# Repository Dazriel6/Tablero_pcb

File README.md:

Tablero de basquetball utilizando dos PCB (potencia y control) para poder comunicarme mediante wifi al tablero y realizar los cambios necesarios.

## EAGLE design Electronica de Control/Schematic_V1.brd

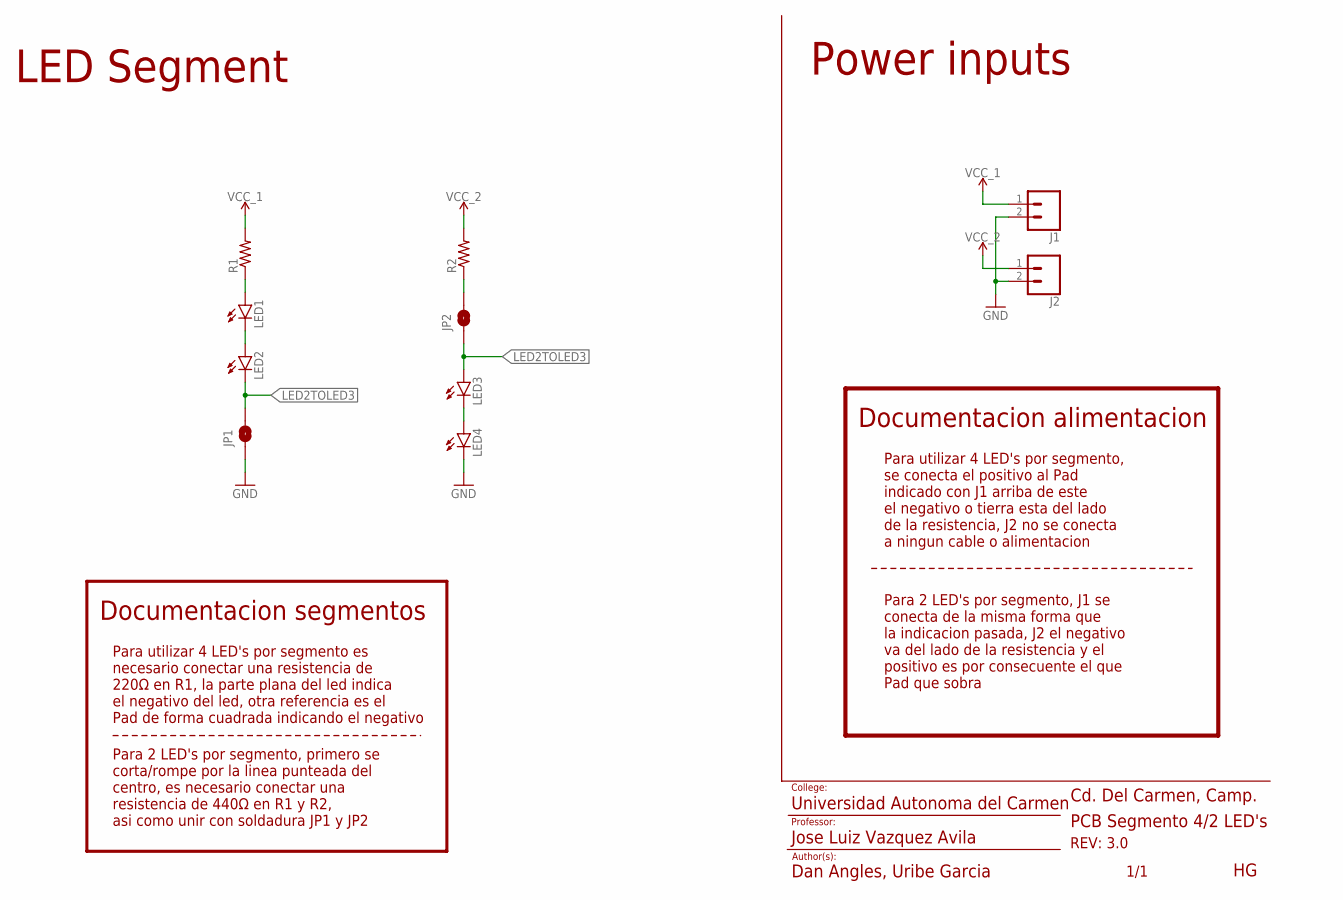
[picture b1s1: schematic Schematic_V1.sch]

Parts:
J1, J2: CONN_02LOCK; 1X02_LOCK
JP1, JP2: JUMPER-SMT_2_NO_SILK_ROUND; SMT-JUMPER_2_NO_SILK_ROUND
LED1, LED2, LED3, LED4: LED10MM
R1, R2: R-US_0411/3V; 0411V

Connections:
GND: J1.2, J2.2, JP1.1, LED4.K (C)
LED2TOLED3: JP1.2, JP2.1, LED2.K (C), LED3.A
unnamed: LED1.K (C), LED2.A
unnamed: LED1.A, R1.1
unnamed: LED3.K (C), LED4.A
unnamed: JP2.2, R2.1
VCC_1: J1.1, R1.2
VCC_2: J2.1, R2.2

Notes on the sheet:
REV: 3.0
Universidad Autonoma del Carmen
Cd. Del Carmen, Camp.
Jose Luiz Vazquez Avila
Dan Angles, Uribe Garcia
College:
Professor:
Author(s):
1/1
LED Segment
Power inputs
Documentacion segmentos
Para utilizar 4 LED's por segmento es necesario conectar una resistencia de 220Ω en R1, la parte plana del led indica el negativo del led, otra referencia es el Pad de forma cuadrada indicando el negativo
Para 2 LED's por segmento, primero se corta/rompe por la linea punteada del centro, es necesario conectar una resistencia de 440Ω en R1 y R2, asi como unir con soldadura JP1 y JP2
Documentacion alimentacion
Para utilizar 4 LED's por segmento, se conecta el positivo al Pad indicado con J1 arriba de este el negativo o tierra esta del lado de la resistencia, J2 no se conecta a ningun cable o alimentacion
Para 2 LED's por segmento, J1 se conecta de la misma forma que la indicacion pasada, J2 el negativo va del lado de la resistencia y el positivo es por consecuente el que Pad que sobra
PCB Segmento 4/2 LED's

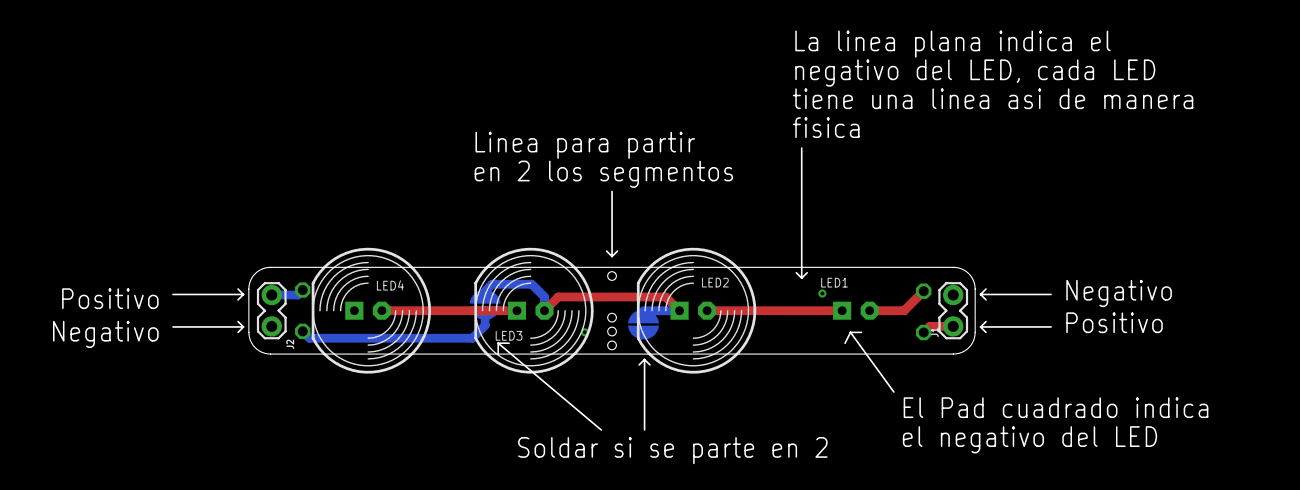
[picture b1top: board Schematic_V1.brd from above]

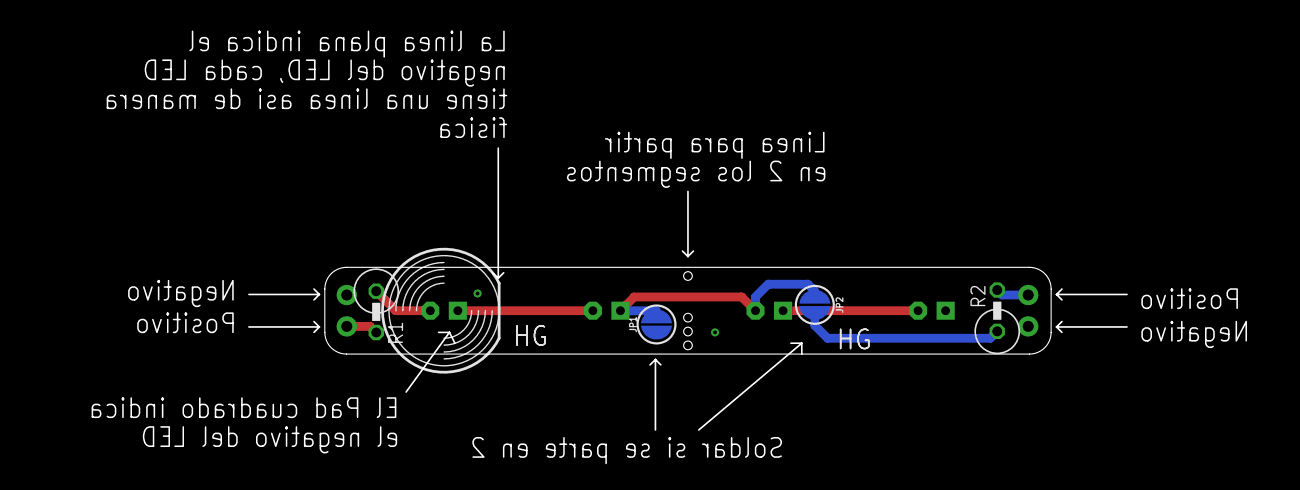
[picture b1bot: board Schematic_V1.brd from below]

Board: 2 copper layers, 115.8 x 41.1 mm, 10 parts (5 on the bottom side), 8 nets.

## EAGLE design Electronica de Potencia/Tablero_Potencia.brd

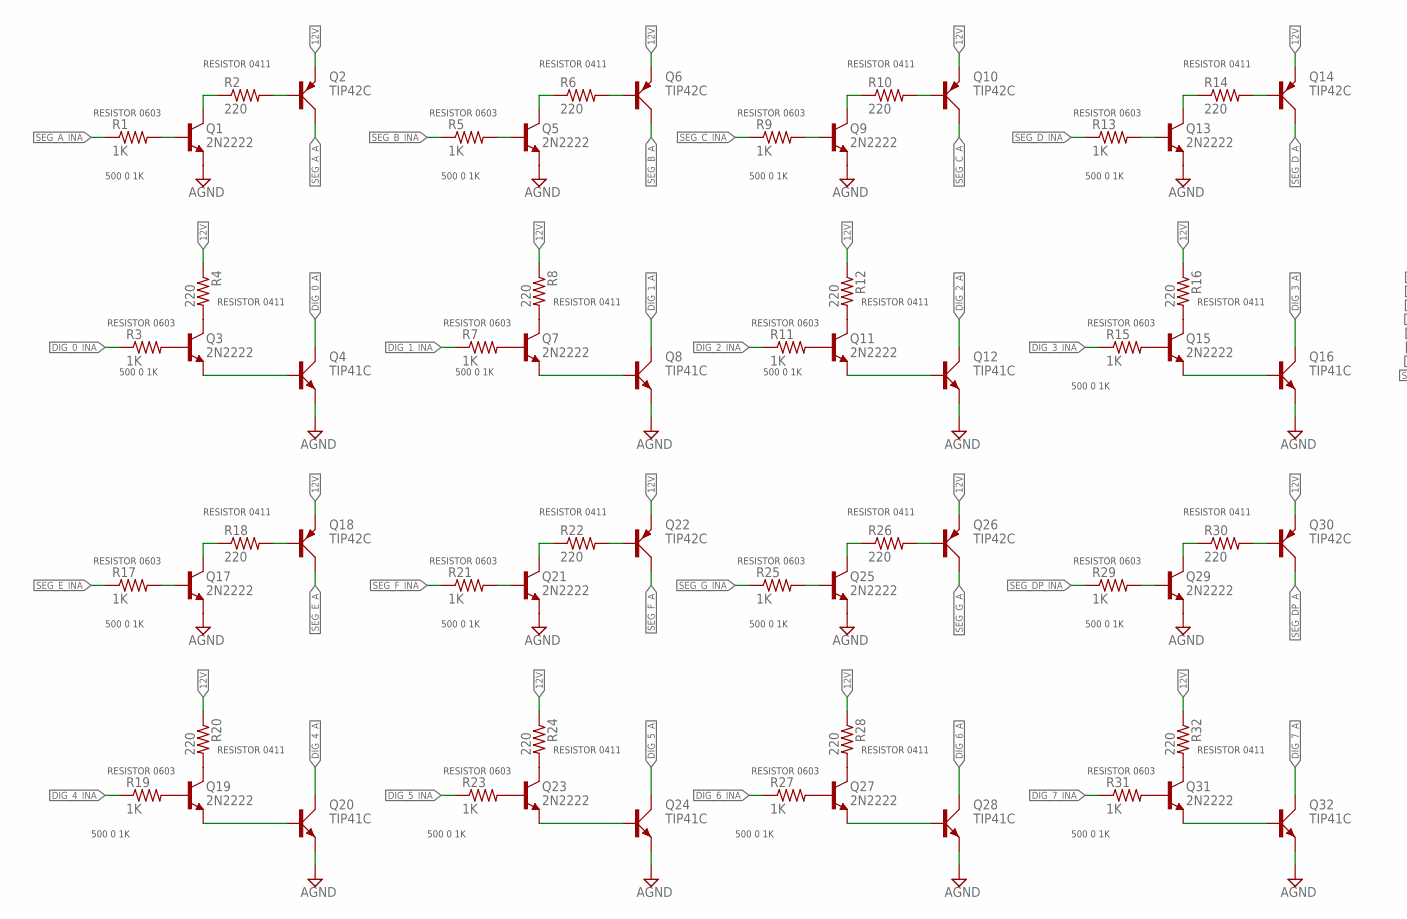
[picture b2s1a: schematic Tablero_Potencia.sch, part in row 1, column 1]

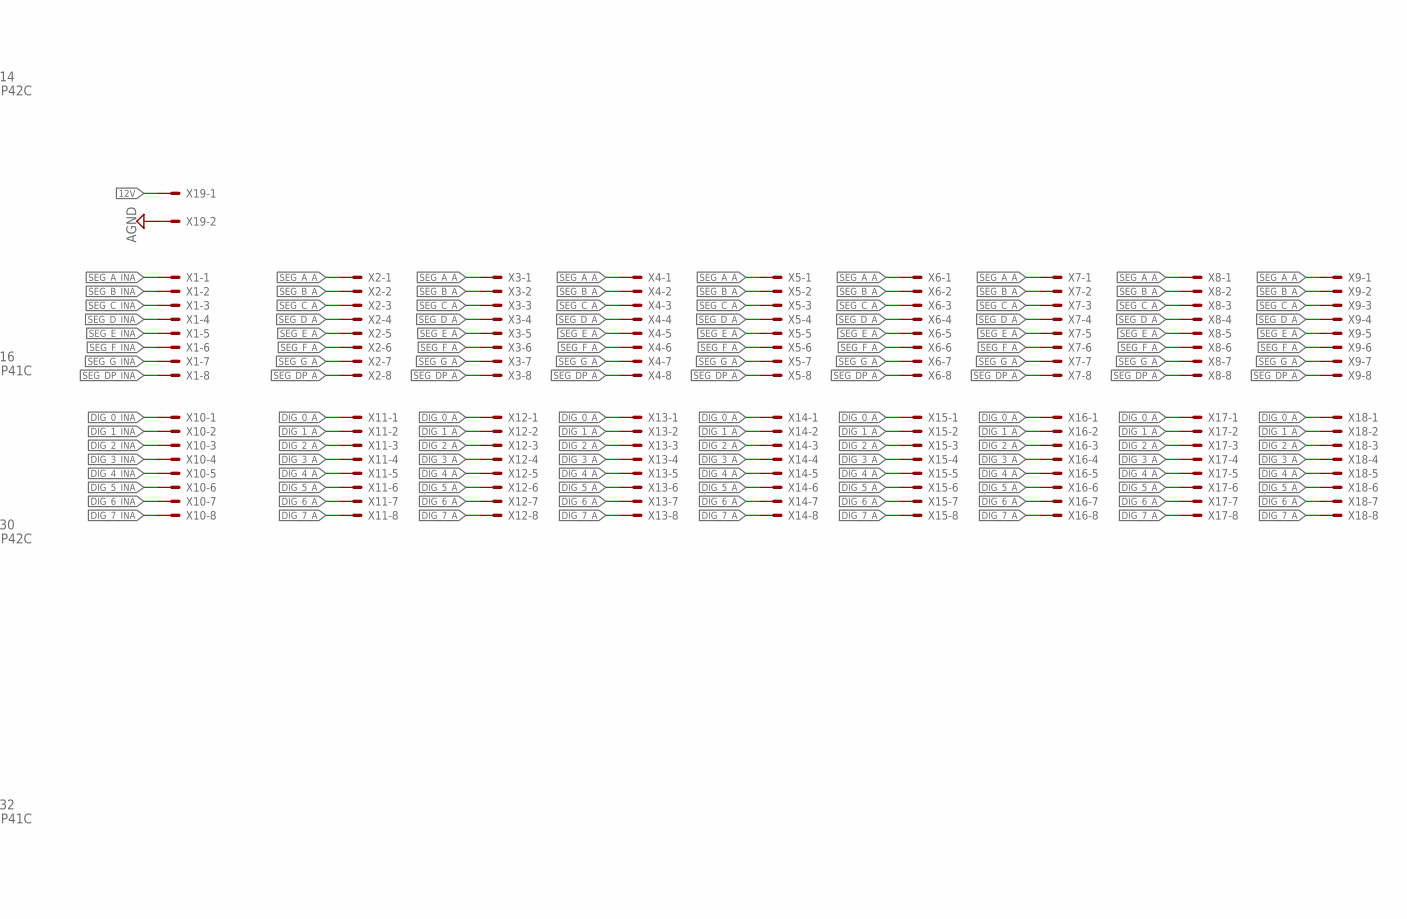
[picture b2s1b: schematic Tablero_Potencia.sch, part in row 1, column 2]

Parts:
Q1, Q3, Q5, Q7, Q9, Q11, Q13, Q15, Q17, Q19, Q21, Q23, Q25, Q27, Q29, Q31: 2N2222; TO92
Q2, Q6, Q10, Q14, Q18, Q22, Q26, Q30: TIP42C; TO220AV
Q4, Q8, Q12, Q16, Q20, Q24, Q28, Q32: TIP41C; TO220AV
R1, R3, R5, R7, R9, R11, R13, R15, R17, R19, R21, R23, R25, R27, R29, R31: 1K; R0603
R2, R4, R6, R8, R10, R12, R14, R16, R18, R20, R22, R24, R26, R28, R30, R32: 220; 0411/15
X1, X2, X3, X4, X5, X6, X7, X8, X9, X10, X11, X12, X13, X14, X15, X16, X17, X18: KK-156-8
X19: KK-156-2

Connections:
12V: Q2.E, Q6.E, Q10.E, Q14.E, Q18.E, Q22.E, Q26.E, Q30.E, R4.1, R8.1, R12.1, R16.1, R20.1, R24.1, R28.1, R32.1, X19.1
AGND: Q1.3 (E), Q4.E, Q5.3 (E), Q8.E, Q9.3 (E), Q12.E, Q13.3 (E), Q16.E, Q17.3 (E), Q20.E, Q21.3 (E), Q24.E, Q25.3 (E), Q28.E, Q29.3 (E), Q32.E, X19.2
DIG_0_A: Q4.C, X11.1, X12.1, X13.1, X14.1, X15.1, X16.1, X17.1, X18.1
DIG_0_INA: R3.1, X10.1
DIG_1_A: Q8.C, X11.2, X12.2, X13.2, X14.2, X15.2, X16.2, X17.2, X18.2
DIG_1_INA: R7.1, X10.2
DIG_2_A: Q12.C, X11.3, X12.3, X13.3, X14.3, X15.3, X16.3, X17.3, X18.3
DIG_2_INA: R11.1, X10.3
DIG_3_A: Q16.C, X11.4, X12.4, X13.4, X14.4, X15.4, X16.4, X17.4, X18.4
DIG_3_INA: R15.1, X10.4
DIG_4_A: Q20.C, X11.5, X12.5, X13.5, X14.5, X15.5, X16.5, X17.5, X18.5
DIG_4_INA: R19.1, X10.5
DIG_5_A: Q24.C, X11.6, X12.6, X13.6, X14.6, X15.6, X16.6, X17.6, X18.6
DIG_5_INA: R23.1, X10.6
DIG_6_A: Q28.C, X11.7, X12.7, X13.7, X14.7, X15.7, X16.7, X17.7, X18.7
DIG_6_INA: R27.1, X10.7
DIG_7_A: Q32.C, X11.8, X12.8, X13.8, X14.8, X15.8, X16.8, X17.8, X18.8
DIG_7_INA: R31.1, X10.8
unnamed: Q2.B, R2.2
unnamed: Q1.1 (C), R2.1
unnamed: Q3.1 (C), R4.2
unnamed: Q3.3 (E), Q4.B
unnamed: Q6.B, R6.2
unnamed: Q7.1 (C), R8.2
unnamed: Q7.3 (E), Q8.B
unnamed: Q5.1 (C), R6.1
unnamed: Q7.2 (B), R7.2
unnamed: Q5.2 (B), R5.2
unnamed: Q3.2 (B), R3.2
unnamed: Q1.2 (B), R1.2
unnamed: Q10.B, R10.2
unnamed: Q11.1 (C), R12.2
unnamed: Q11.3 (E), Q12.B
unnamed: Q9.1 (C), R10.1
unnamed: Q11.2 (B), R11.2
unnamed: Q9.2 (B), R9.2
unnamed: Q14.B, R14.2
unnamed: Q15.1 (C), R16.2
unnamed: Q15.3 (E), Q16.B
unnamed: Q13.1 (C), R14.1
unnamed: Q15.2 (B), R15.2
unnamed: Q13.2 (B), R13.2
unnamed: Q18.B, R18.2
unnamed: Q19.1 (C), R20.2
unnamed: Q19.3 (E), Q20.B
unnamed: Q17.1 (C), R18.1
unnamed: Q19.2 (B), R19.2
unnamed: Q17.2 (B), R17.2
unnamed: Q22.B, R22.2
unnamed: Q23.1 (C), R24.2
unnamed: Q23.3 (E), Q24.B
unnamed: Q21.1 (C), R22.1
unnamed: Q23.2 (B), R23.2
unnamed: Q21.2 (B), R21.2
unnamed: Q26.B, R26.2
unnamed: Q27.1 (C), R28.2
unnamed: Q27.3 (E), Q28.B
unnamed: Q25.1 (C), R26.1
unnamed: Q27.2 (B), R27.2
unnamed: Q25.2 (B), R25.2
unnamed: Q30.B, R30.2
unnamed: Q31.1 (C), R32.2
unnamed: Q31.3 (E), Q32.B
unnamed: Q29.1 (C), R30.1
unnamed: Q31.2 (B), R31.2
unnamed: Q29.2 (B), R29.2
SEG_A_A: Q2.C, X2.1, X3.1, X4.1, X5.1, X6.1, X7.1, X8.1, X9.1
SEG_A_INA: R1.1, X1.1
SEG_B_A: Q6.C, X2.2, X3.2, X4.2, X5.2, X6.2, X7.2, X8.2, X9.2
SEG_B_INA: R5.1, X1.2
SEG_C_A: Q10.C, X2.3, X3.3, X4.3, X5.3, X6.3, X7.3, X8.3, X9.3
SEG_C_INA: R9.1, X1.3
SEG_DP_A: Q30.C, X2.8, X3.8, X4.8, X5.8, X6.8, X7.8, X8.8, X9.8
SEG_DP_INA: R29.1, X1.8
SEG_D_A: Q14.C, X2.4, X3.4, X4.4, X5.4, X6.4, X7.4, X8.4, X9.4
SEG_D_INA: R13.1, X1.4
SEG_E_A: Q18.C, X2.5, X3.5, X4.5, X5.5, X6.5, X7.5, X8.5, X9.5
SEG_E_INA: R17.1, X1.5
SEG_F_A: Q22.C, X2.6, X3.6, X4.6, X5.6, X6.6, X7.6, X8.6, X9.6
SEG_F_INA: R21.1, X1.6
SEG_G_A: Q26.C, X2.7, X3.7, X4.7, X5.7, X6.7, X7.7, X8.7, X9.7
SEG_G_INA: R25.1, X1.7

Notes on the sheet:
RESISTOR 0411
RESISTOR 0603
500 0 1K

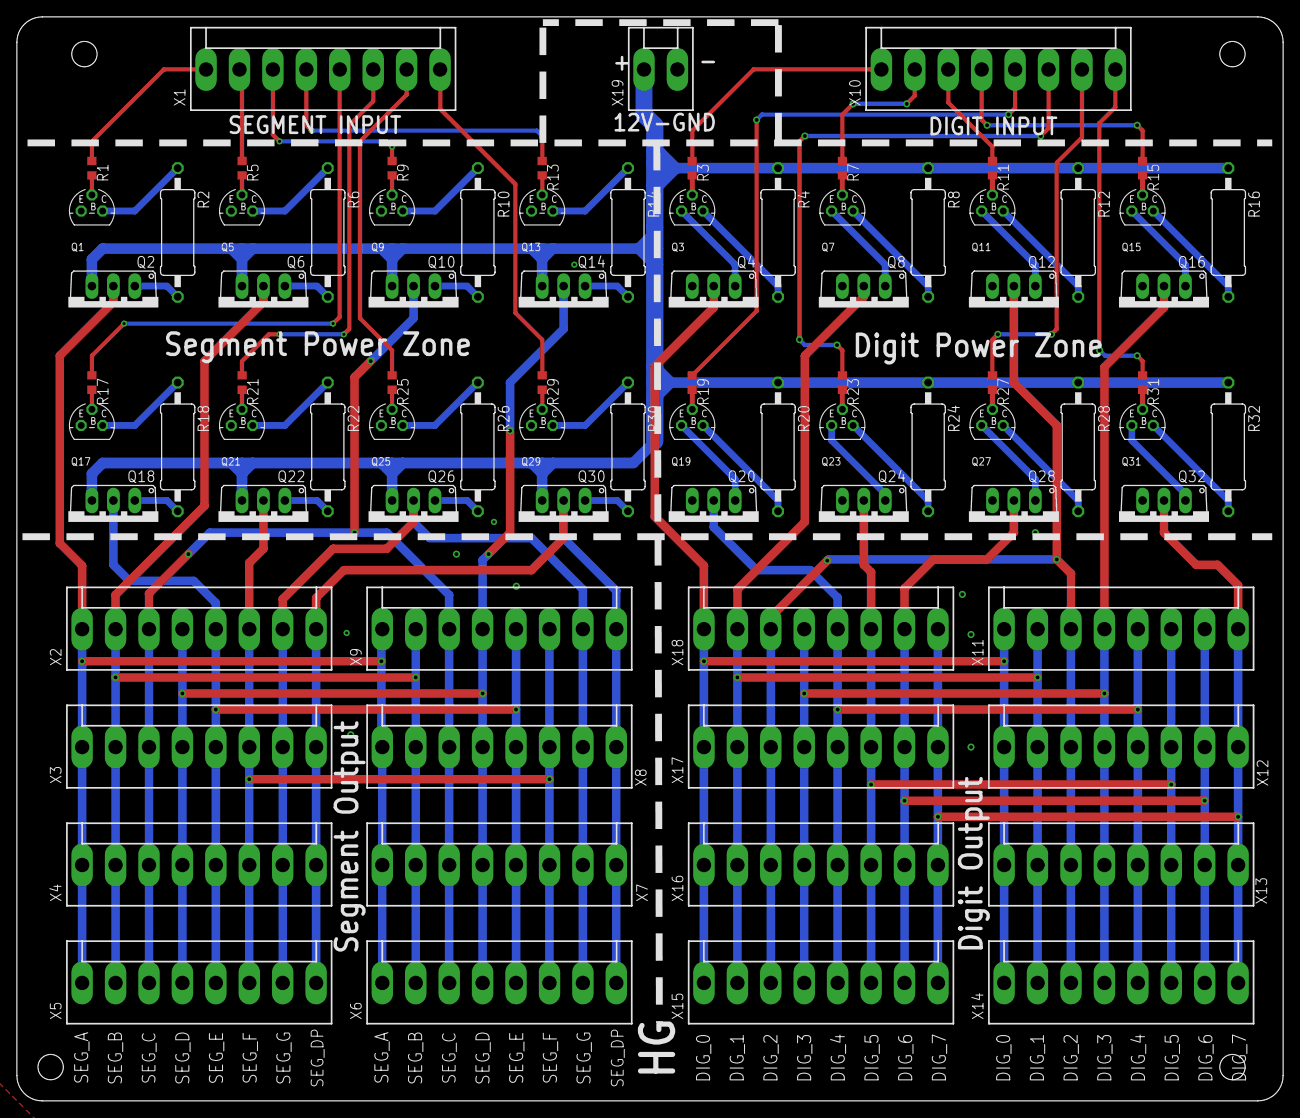
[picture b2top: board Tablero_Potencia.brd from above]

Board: 2 copper layers, 150.0 x 128.4 mm, 83 parts (0 on the bottom side), 82 nets.

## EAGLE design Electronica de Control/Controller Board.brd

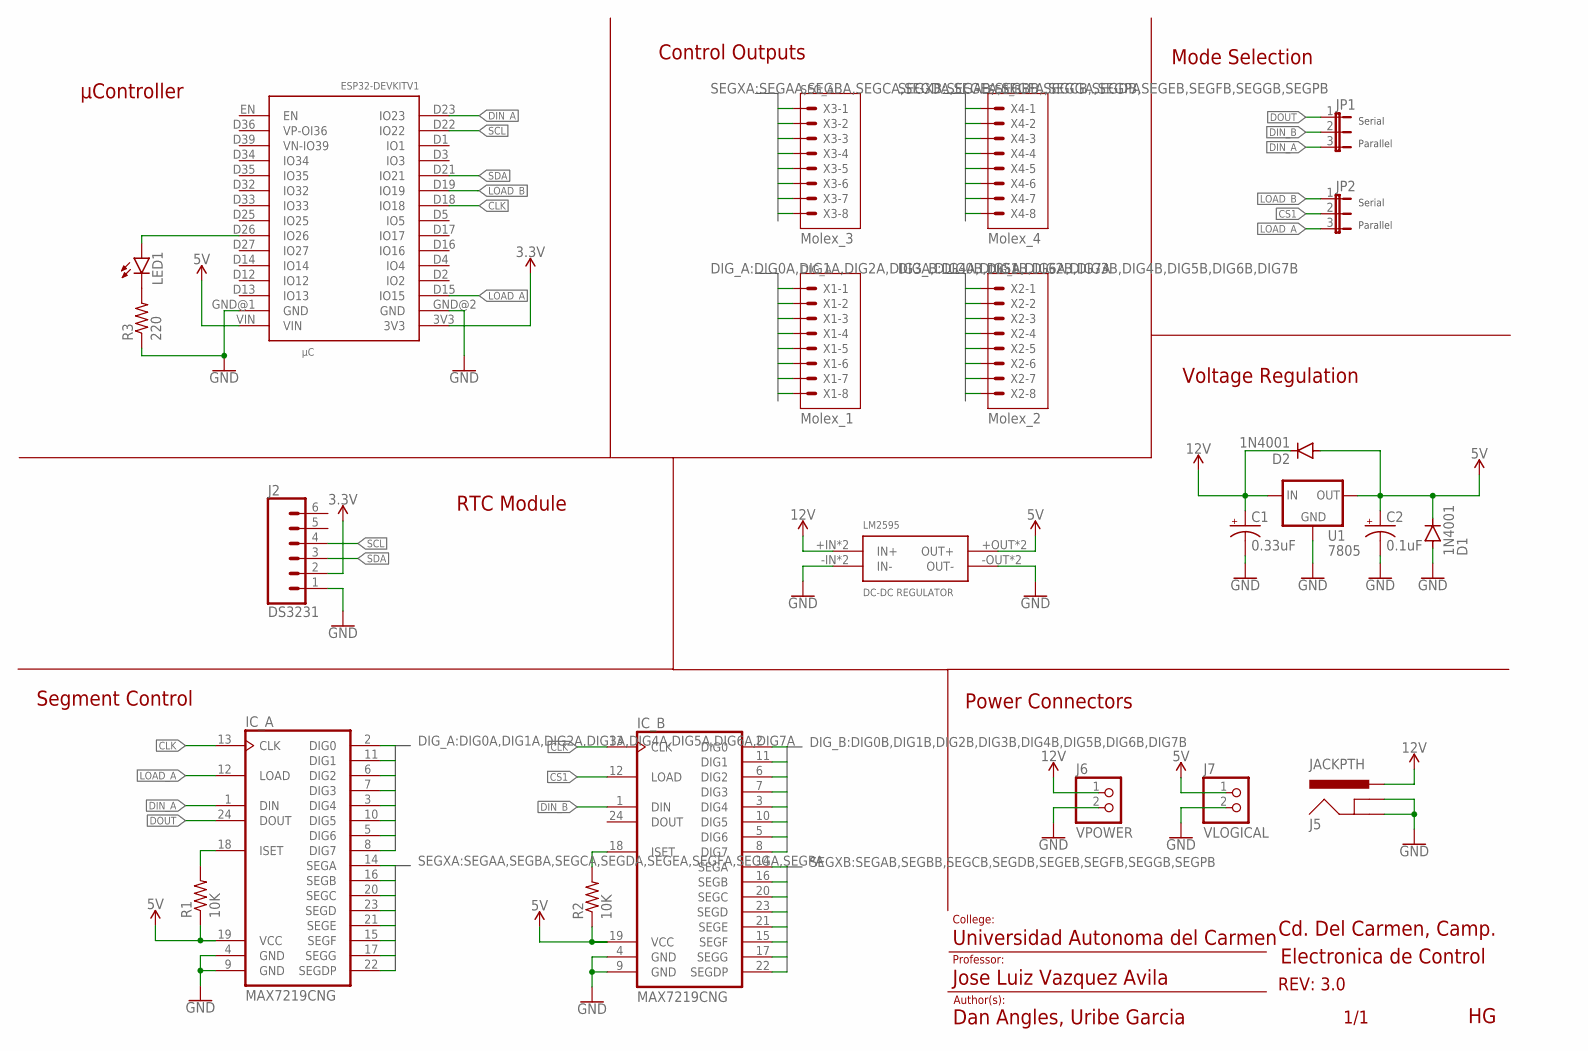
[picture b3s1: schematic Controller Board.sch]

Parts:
C1: 0.33uF; E3,5-8
C2: 0.1uF; E2-5
D1, D2: 1N4001; DO41-10
IC_A: MAX7219CNG; DIL24-3
IC_B: MAX7219CNG; DIL24-3
J2: DS3231; 1X06_FEMALE_LOCK.010
J5: JACKPTH; POWER_JACK_PTH_LOCK
J6: VPOWER; 1X02
J7: VLOGICAL; 1X02
JP1, JP2: JP2E; JP2
LED1: LEDCHIP-LED0805; CHIP-LED0805
R1, R2: 10K; 0204/7
R3: 220; R0805
U1: 7805; 78XXL
U$1: MODULE_LM2595
X1, X2, X3, X4: KK-156-8
μC: ESP32DEVKITV1; ESP32-DEVKITV1

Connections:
3.3V: J2.2, μC.3V3
5V: C2.+, D1.C, D2.A, IC_A.19 (VCC), IC_B.19 (VCC), J7.1, R1.1, R2.1, U1.OUT, U$1.+OUT (OUT+), U$1.+OUTSMD (OUT+), μC.VIN
12V: C1.+, D2.C, J5.PWR, J6.1, U1.IN, U$1.+IN (IN+), U$1.+INSMD (IN+)
CLK: IC_A.13 (CLK), IC_B.13 (CLK), μC.D18 (IO18)
CS1: IC_B.12 (LOAD), JP2.2
DIG0A: IC_A.2 (DIG0), X1.1
DIG0B: IC_B.2 (DIG0), X2.1
DIG1A: IC_A.11 (DIG1), X1.2
DIG1B: IC_B.11 (DIG1), X2.2
DIG2A: IC_A.6 (DIG2), X1.3
DIG2B: IC_B.6 (DIG2), X2.3
DIG3A: IC_A.7 (DIG3), X1.4
DIG3B: IC_B.7 (DIG3), X2.4
DIG4A: IC_A.3 (DIG4), X1.5
DIG4B: IC_B.3 (DIG4), X2.5
DIG5A: IC_A.10 (DIG5), X1.6
DIG5B: IC_B.10 (DIG5), X2.6
DIG6A: IC_A.5 (DIG6), X1.7
DIG6B: IC_B.5 (DIG6), X2.7
DIG7A: IC_A.8 (DIG7), X1.8
DIG7B: IC_B.8 (DIG7), X2.8
DIN_A: IC_A.1 (DIN), JP1.3, μC.D23 (IO23)
DIN_B: IC_B.1 (DIN), JP1.2
DOUT: IC_A.24 (DOUT), JP1.1
GND: C1.-, C2.-, D1.A, IC_A.4 (GND), IC_A.9 (GND), IC_B.4 (GND), IC_B.9 (GND), J2.1, J5.GND, J5.GNDBREAK, J6.2, J7.2, R3.1, U1.GND, U$1.-IN (IN-), U$1.-INSMD (IN-), U$1.-OUT (OUT-), U$1.-OUTSMD (OUT-), μC.GND@1 (GND), μC.GND@2 (GND)
ISET-A: IC_A.18 (ISET), R1.2
ISET-B: IC_B.18 (ISET), R2.2
LOAD_A: IC_A.12 (LOAD), JP2.3, μC.D15 (IO15)
LOAD_B: JP2.1, μC.D19 (IO19)
unnamed: LED1.A, μC.D26 (IO26)
unnamed: LED1.C, R3.2
SCL: J2.4, μC.D22 (IO22)
SDA: J2.3, μC.D21 (IO21)
SEGAA: IC_A.14 (SEGA), X3.1
SEGAB: IC_B.14 (SEGA), X4.1
SEGBA: IC_A.16 (SEGB), X3.2
SEGBB: IC_B.16 (SEGB), X4.2
SEGCA: IC_A.20 (SEGC), X3.3
SEGCB: IC_B.20 (SEGC), X4.3
SEGDA: IC_A.23 (SEGD), X3.4
SEGDB: IC_B.23 (SEGD), X4.4
SEGEA: IC_A.21 (SEGE), X3.5
SEGEB: IC_B.21 (SEGE), X4.5
SEGFA: IC_A.15 (SEGF), X3.6
SEGFB: IC_B.15 (SEGF), X4.6
SEGGA: IC_A.17 (SEGG), X3.7
SEGGB: IC_B.17 (SEGG), X4.7
SEGPA: IC_A.22 (SEGDP), X3.8
SEGPB: IC_B.22 (SEGDP), X4.8

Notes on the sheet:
Serial
Parallel
REV: 3.0
Universidad Autonoma del Carmen
Cd. Del Carmen, Camp.
Jose Luiz Vazquez Avila
Dan Angles, Uribe Garcia
College:
Professor:
Author(s):
μController
Segment Control
Power Connectors
Control Outputs
Voltage Regulation
Mode Selection
Molex_1
Molex_3
Molex_4
Molex_2
SEG_B
SEG_A
DIG_A
DIG_B
1/1
RTC Module
Electronica de Control

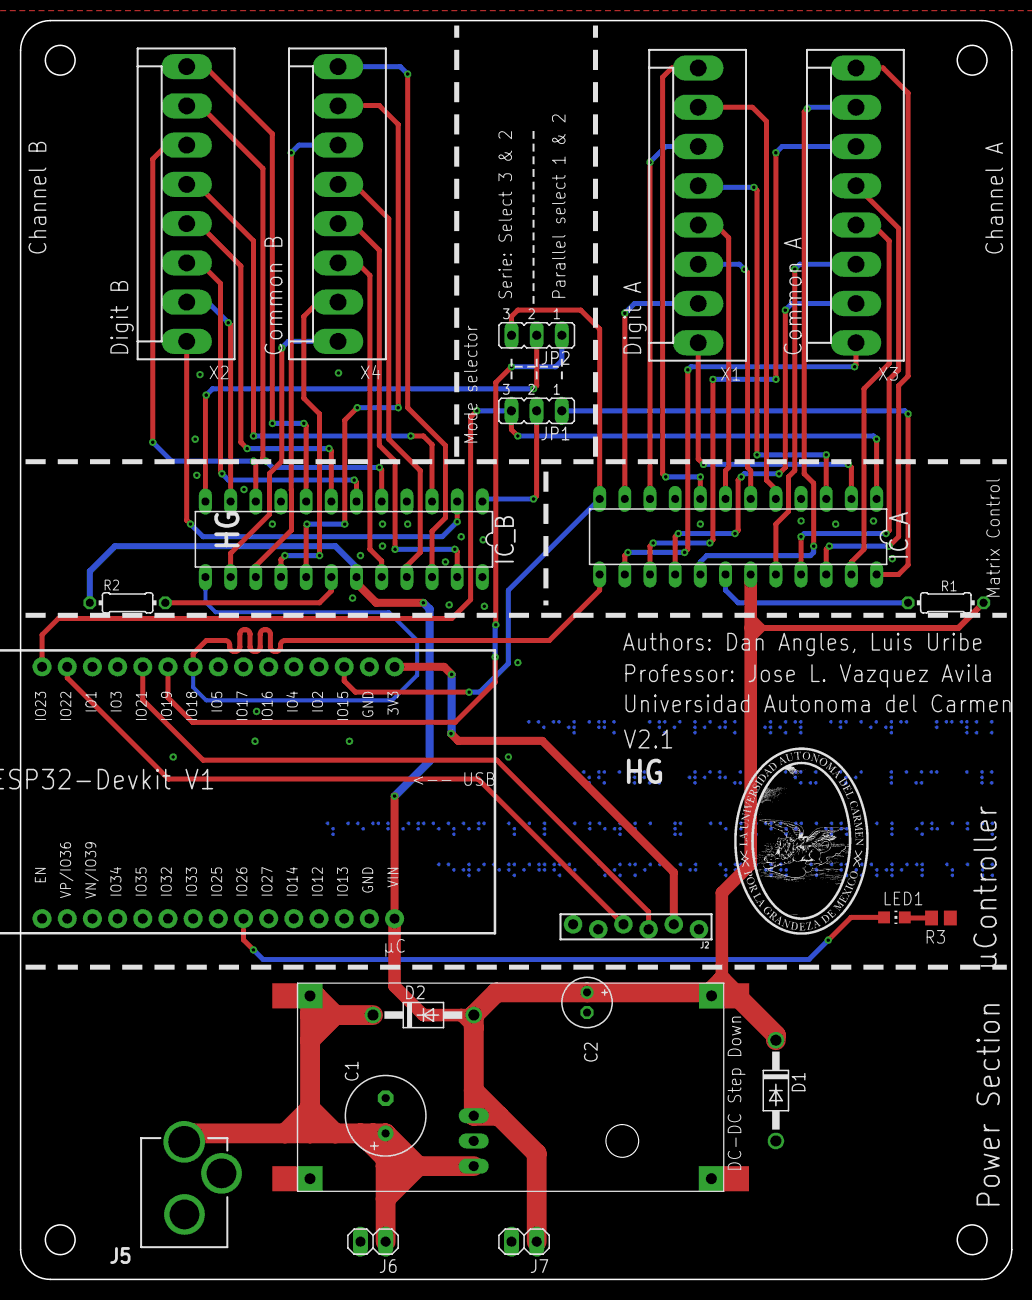
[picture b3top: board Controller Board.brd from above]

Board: 2 copper layers, 100.0 x 127.0 mm, 23 parts (1 on the bottom side), 49 nets.

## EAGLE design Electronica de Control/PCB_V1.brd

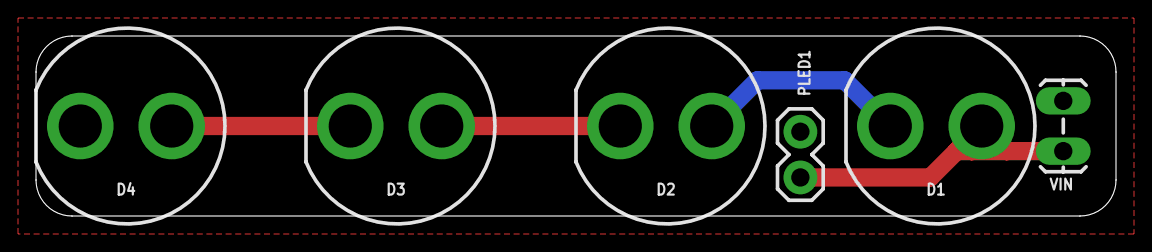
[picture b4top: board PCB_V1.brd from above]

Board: 2 copper layers, 60.0 x 10.0 mm, 6 parts (0 on the bottom side), 5 nets.

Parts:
D1, D2, D3, D4: LED_10MM
PLED1: 1X02
VIN: 1X02_LOCK_LONGPADS

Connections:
GND: D4.C, PLED1.2, VIN.2
unnamed: D1.C, D2.A
unnamed: D2.C, D3.A
unnamed: D3.C, D4.A
VCC: D1.A, PLED1.1, VIN.1

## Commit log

2023-05-12 first commit, subida de archivos generados

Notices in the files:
parts and their libraries:
SparkFun-Connectors: Licensing: Creative Commons ShareAlike 4.0 International - https://creativecommons.org/licenses/by-sa/4.0
